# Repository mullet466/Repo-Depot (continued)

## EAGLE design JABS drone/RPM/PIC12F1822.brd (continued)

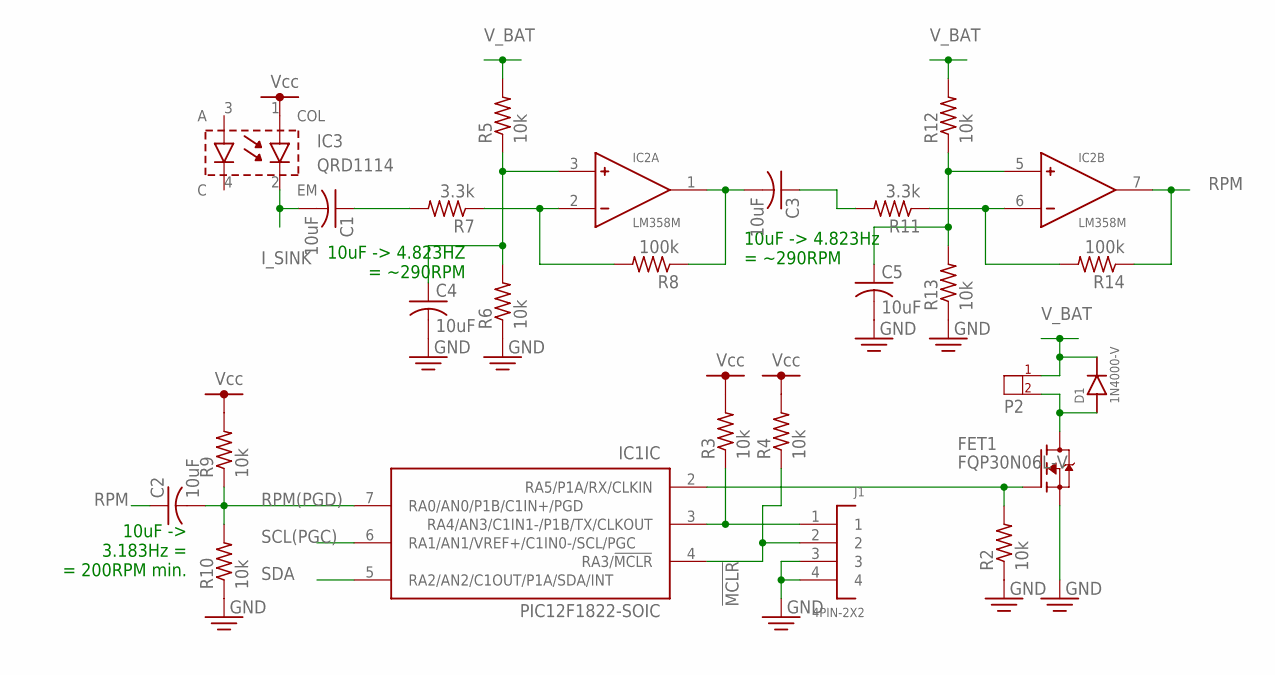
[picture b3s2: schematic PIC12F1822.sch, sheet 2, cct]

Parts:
C1, C2, C3, C4, C5: 10uF; C0805
D1: 1N4000-V; DIODE-V
FET1: FQP30N06L-V; TO220V
IC1: PIC12F1822-SOIC; 8-SOP
IC2: LM358M; 8-SOP
IC3: QRD1114
J1: 4PIN-2X2; 4P-2X2
P2: CONN-2P-PNI; B02B-PNISK
R2, R3, R4, R5, R6, R9, R10, R12, R13: 10k; R0805
R7, R11: 3.3k; R0805
R8, R14: 100k; R0805

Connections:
!MCLR: IC1.4 (RA3/!MCLR), J1.2, R4.1; also elsewhere on the board
GND: C4.2, C5.2, FET1.3 (S), J1.3, J1.4, R2.1, R6.1, R10.1, R13.1; also elsewhere on the board
I_SINK: C1.2, IC3.2 (EM); also elsewhere on the board
unnamed: FET1.1 (G), IC1.2 (RA5/P1A/RX/CLKIN), R2.2
unnamed: D1.A, FET1.2 (D), P2.2
unnamed: IC1.3 (RA4/AN3/C1IN1-/P1B/TX/CLKOUT), J1.1, R3.1
unnamed: C4.1, IC2.3 (+), R5.1, R6.2
unnamed: IC2.2 (-), R7.1, R8.2
unnamed: C1.1, R7.2
unnamed: C3.2, IC2.1 (OUT), R8.1
unnamed: C3.1, R11.2
unnamed: C5.1, IC2.5 (+), R12.1, R13.2
unnamed: IC2.6 (-), R11.1, R14.2
RPM: C2.1, IC2.7 (OUT), R14.1
RPM(PGD): C2.2, IC1.7 (RA0/AN0/P1B/C1IN+/PGD), R9.1, R10.2; also elsewhere on the board
SCL(PGC): IC1.6 (RA1/AN1/VREF+/C1IN0-/SCL/PGC); also elsewhere on the board
SDA: IC1.5 (RA2/AN2/C1OUT/P1A/SDA/INT); also elsewhere on the board
VCC: IC3.1 (COL), R3.2, R4.2, R9.2; also elsewhere on the board
V_BAT: D1.C, P2.1, R5.2, R12.2; also elsewhere on the board

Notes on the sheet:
10uF -> 4.823HZ = ~290RPM
10uF -> 4.823Hz = ~290RPM
10uF -> 3.183Hz = = 200RPM min.

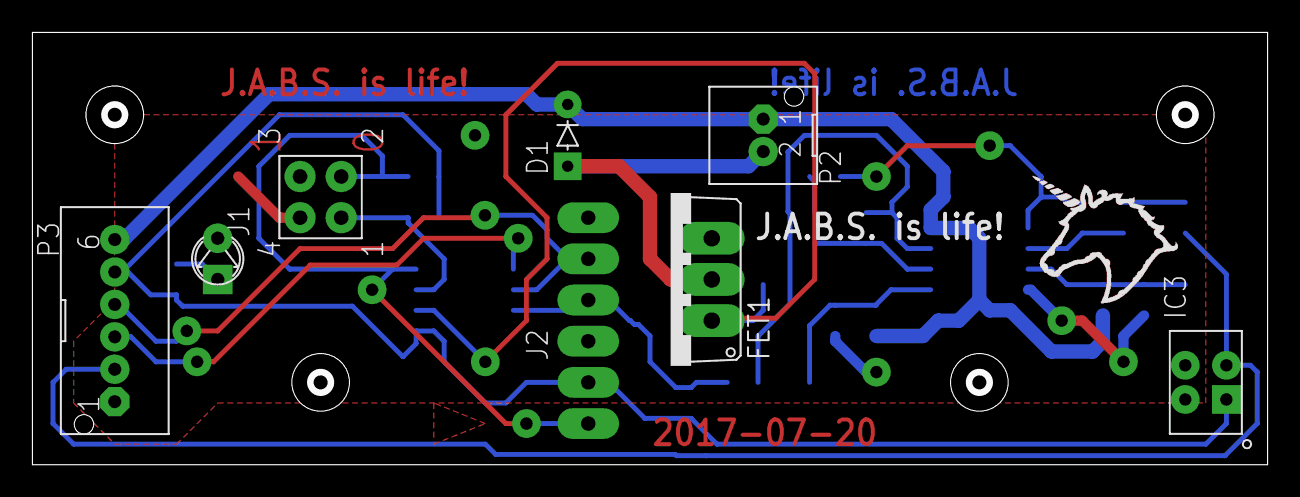
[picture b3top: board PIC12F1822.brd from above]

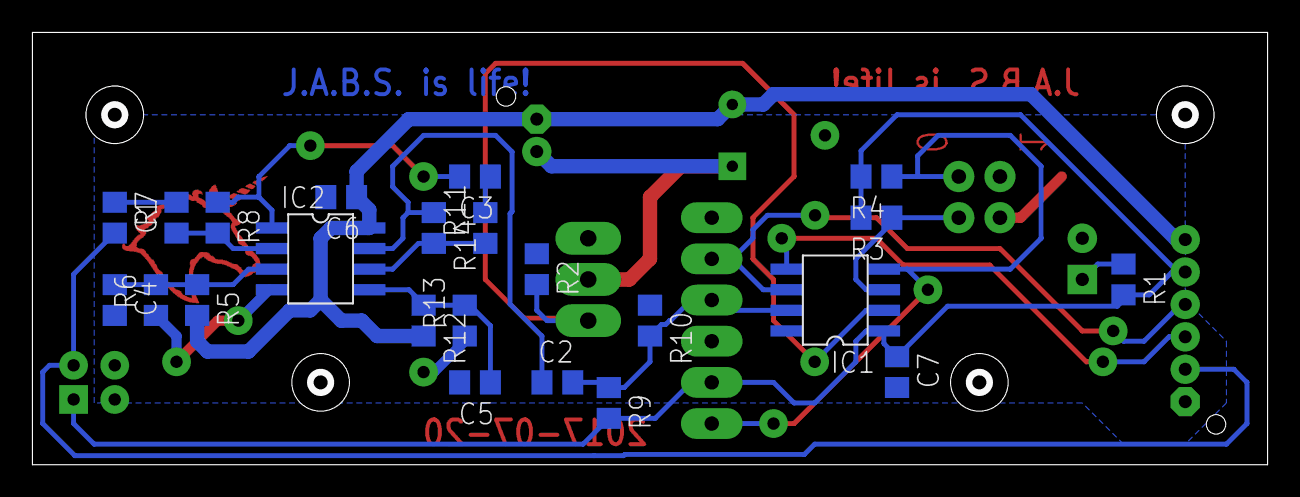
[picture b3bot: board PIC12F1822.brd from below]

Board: 2 copper layers, 75.8 x 26.3 mm, 37 parts (23 on the bottom side), 20 nets.

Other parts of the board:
U$16, U$17, U$18, U$19: #6-32
U$20: UNICORN-TOP
U$21: UNICORN-SCREEN

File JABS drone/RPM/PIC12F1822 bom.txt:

"Qty";"Value";"Device";"Package";"Parts";"Description";"";
"2";"100k";"R-US_R0805";"R0805";"R8, R14";"RESISTOR, American symbol";"";
"9";"10k";"R-US_R0805";"R0805";"R2, R3, R4, R5, R6, R9, R10, R12, R13";"RESISTOR, American symbol";"";
"3";"10uF";"C-USC0805";"C0805";"C1, C2, C3";"CAPACITOR, American symbol";"";
"1";"1N4000-V";"1N4000-V";"DIODE-V";"D1";"";"";
"2";"3.3k";"R-US_R0805";"R0805";"R7, R11";"RESISTOR, American symbol";"";
"1";"330";"R-US_R0805";"R0805";"R1";"RESISTOR, American symbol";"";
"1";"4PIN-2X2";"4PIN-2X2";"4P-2X2";"J1";"";"";
"1";"Bruno";"LED3MM";"LED3MM";"LED1";"";"";
"1";"CONN-2P-PNI";"CONN-2P-PNI";"B02B-PNISK";"P2";"";"";
"1";"CONN-6P-PNI";"CONN-6P-PNI";"B06B-PNISK";"P3";"";"";
"1";"FQP30N06L-V";"FQP30N06L-V";"TO220V";"FET1";"";"";
"1";"LM358M";"LM358M";"8-SOP";"IC2";"";"";
"1";"PIC12F1822-SOIC";"PIC12F1822-SOIC";"8-SOP";"IC1";"";"";
"1";"PICKIT3";"PICKIT3";"PICKIT3";"J2";"";"";
"1";"QRD1114";"QRD1114";"QRD1114";"IC3";"";"";

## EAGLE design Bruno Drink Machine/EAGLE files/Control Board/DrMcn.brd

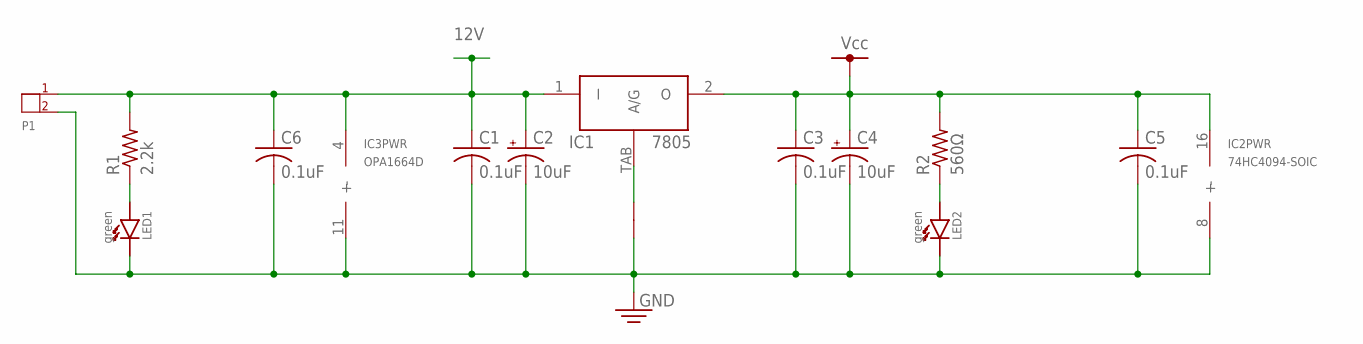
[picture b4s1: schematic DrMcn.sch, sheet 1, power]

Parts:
-1: SEPERATOR
C1, C3, C5, C6: 0.1uF; C0805
C2, C4: 10uF; E5-10,5
IC1: 7805; TO-252
IC2: 74HC4094-SOIC; 16-SOIC
IC3: OPA1664D; 14-SOP
LED1, LED2: green; 0603-LED
P1: CONN-2P-VL; B02P-VL
R1: 2.2k; R0805
R2: 560Ω; R0603

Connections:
12V: C1.1, C2.+, C6.1, IC1.1 (I), IC3.4 (+), P1.1, R1.2; also elsewhere on the board
GND: -1.P$1, C1.2, C2.-, C3.2, C4.-, C5.2, C6.2, IC2.8 (-), IC3.11 (-), LED1.C, LED2.C, P1.2; also elsewhere on the board
unnamed: LED2.A, R2.1
unnamed: LED1.A, R1.1
TAB: -1.P$2, IC1.TAB (A/G)
VCC: C3.1, C4.+, C5.1, IC1.2 (O), IC2.16 (+), R2.2; also elsewhere on the board

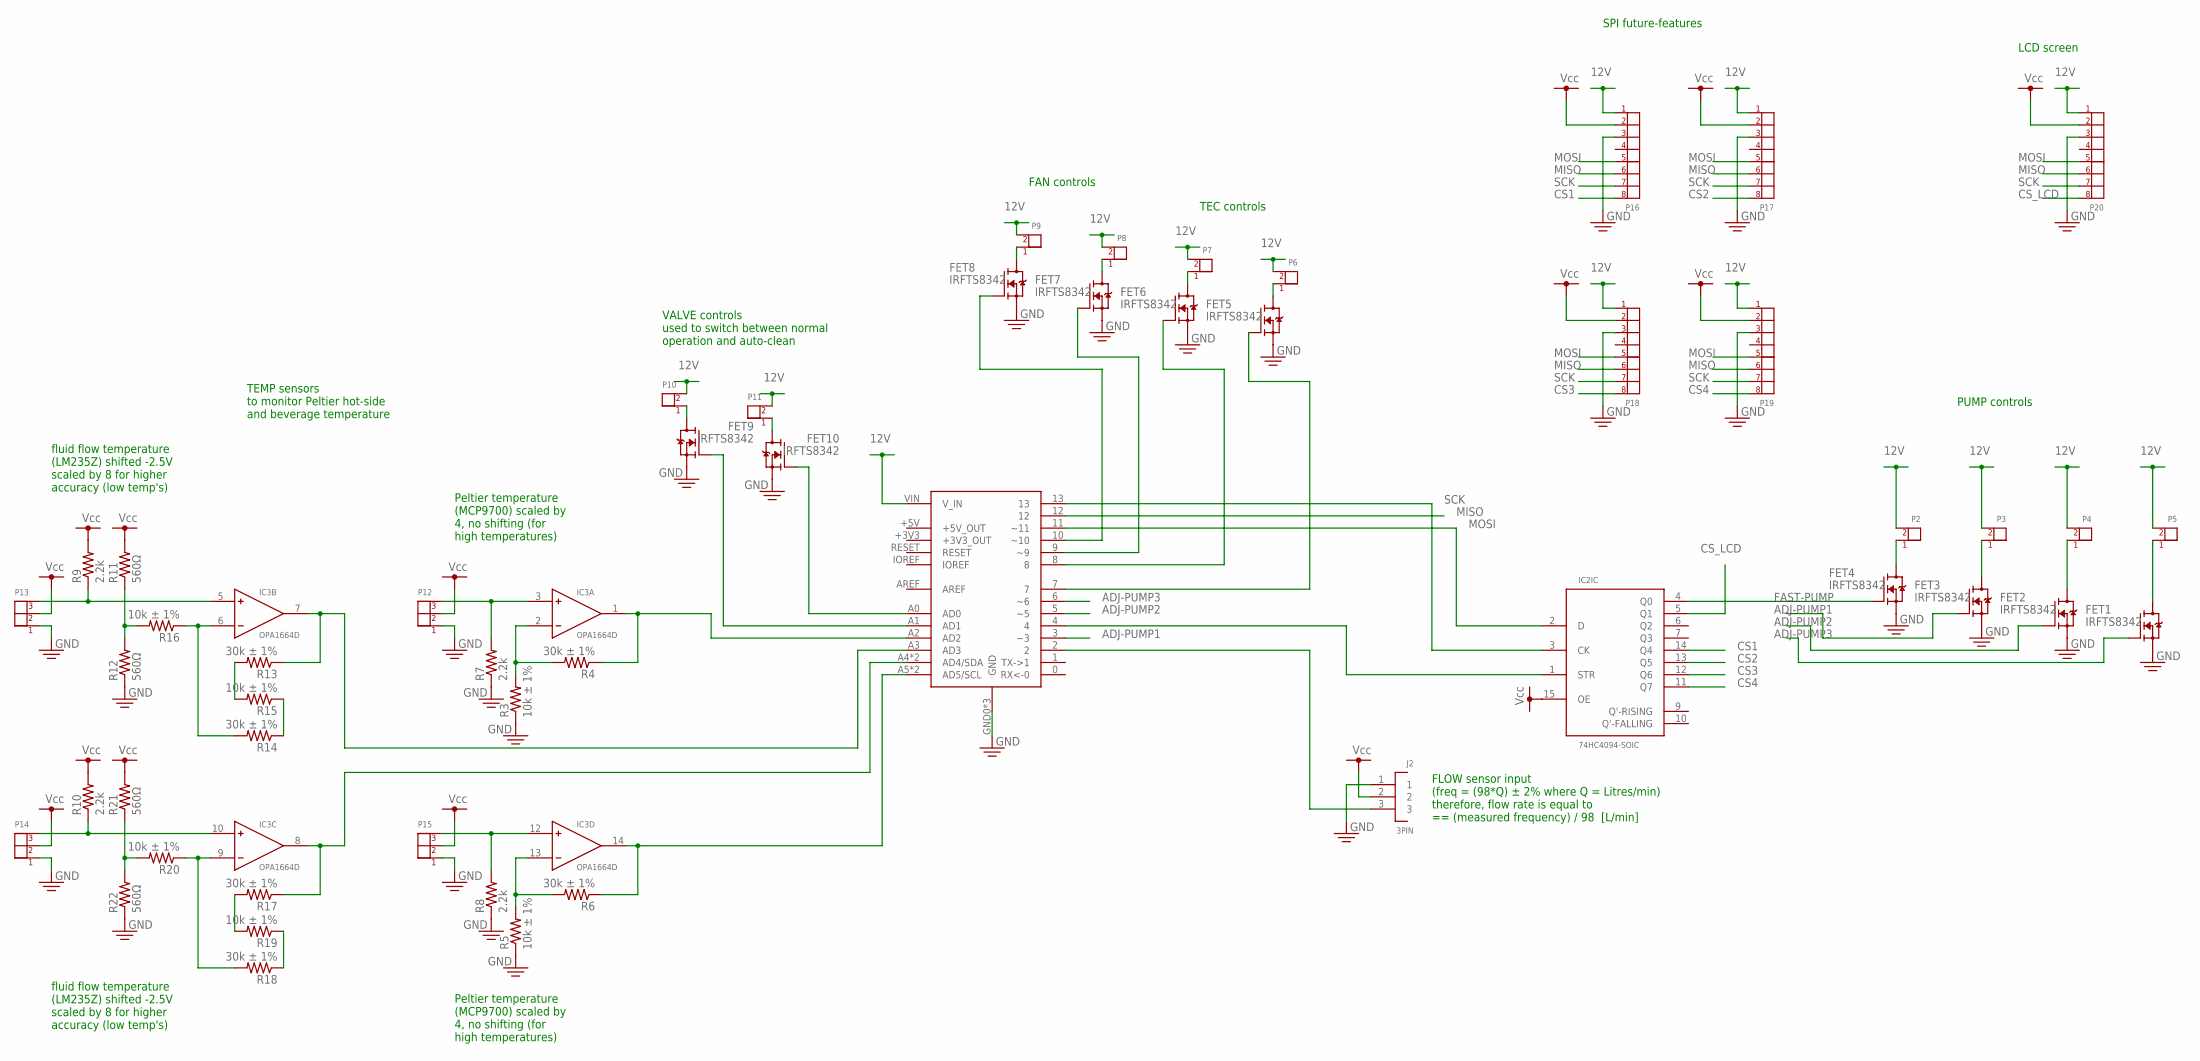
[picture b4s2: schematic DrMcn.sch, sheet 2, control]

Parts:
FET1, FET2, FET3, FET4, FET5, FET6, FET7, FET8, FET9, FET10: IRFTS8342; SOT23-6
IC2: 74HC4094-SOIC; 16-SOIC
IC3: OPA1664D; 14-SOP
J1: ARDUINO_UNO
J2: 3PIN; 3P
P2, P3, P4, P5, P8, P9, P10, P11: CONN-2P-PNI; B02B-PNISK
P6, P7: CONN-2P-VL; B02P-VL
P12, P13, P14, P15: CONN-3P-PNI; B03B-PNISK
P16, P17, P18, P19, P20: CONN-8P-PND; B08B-PND
R3, R5, R15, R16, R19, R20: 10k ± 1%; R0603
R4, R6, R13, R14, R17, R18: 30k ± 1%; R0603
R7, R8, R9, R10: 2.2k; R0603
R11, R12, R21, R22: 560Ω; R0603

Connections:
12V: J1.VIN (V_IN), P2.2, P3.2, P4.2, P5.2, P6.2, P7.2, P8.2, P9.2, P10.2, P11.2, P16.1, P17.1, P18.1, P19.1, P20.1; also elsewhere on the board
ADJ-PUMP1: FET3.3 (G), J1.3 (~3)
ADJ-PUMP2: FET2.3 (G), J1.5 (~5)
ADJ-PUMP3: FET1.3 (G), J1.6 (~6)
CS1: IC2.14 (Q4), P16.8
CS2: IC2.13 (Q5), P17.8
CS3: IC2.12 (Q6), P18.8
CS4: IC2.11 (Q7), P19.8
CS_LCD: IC2.5 (Q1), P20.8
FAST-PUMP: FET4.3 (G), IC2.4 (Q0)
GND: FET1.4 (S), FET2.4 (S), FET3.4 (S), FET4.4 (S), FET5.4 (S), FET6.4 (S), FET7.4 (S), FET8.4 (S), FET9.4 (S), FET10.4 (S), J1.GND0 (GND), J1.GND1 (GND), J1.GND2 (GND), J2.1, P12.1, P13.1, P14.1, P15.1, P16.3, P17.3, P18.3, P19.3, P20.3, R3.1, R5.1, R7.1, R8.1, R12.1, R22.1; also elsewhere on the board
MISO: J1.12, P16.6, P17.6, P18.6, P19.6, P20.6
MOSI: IC2.2 (D), J1.11 (~11), P16.5, P17.5, P18.5, P19.5, P20.5
unnamed: IC3.7 (OUT), J1.A3 (AD3), R13.1
unnamed: IC3.10 (+), P14.3, R10.1
unnamed: IC3.2 (-), R3.2, R4.2
unnamed: IC3.1 (OUT), J1.A2 (AD2), R4.1
unnamed: FET4.1 (D), FET4.2 (D), FET4.5 (D), FET4.6 (D), P2.1
unnamed: FET3.1 (D), FET3.2 (D), FET3.5 (D), FET3.6 (D), P3.1
unnamed: FET2.1 (D), FET2.2 (D), FET2.5 (D), FET2.6 (D), P4.1
unnamed: FET1.1 (D), FET1.2 (D), FET1.5 (D), FET1.6 (D), P5.1
unnamed: FET7.3 (G), J1.9 (~9)
unnamed: J1.2, J2.3
unnamed: FET9.1 (D), FET9.2 (D), FET9.5 (D), FET9.6 (D), P10.1
unnamed: FET5.1 (D), FET5.2 (D), FET5.5 (D), FET5.6 (D), P6.1
unnamed: FET10.1 (D), FET10.2 (D), FET10.5 (D), FET10.6 (D), P11.1
unnamed: FET6.1 (D), FET6.2 (D), FET6.5 (D), FET6.6 (D), P7.1
unnamed: FET7.1 (D), FET7.2 (D), FET7.5 (D), FET7.6 (D), P8.1
unnamed: FET8.3 (G), J1.10 (~10)
unnamed: FET8.1 (D), FET8.2 (D), FET8.5 (D), FET8.6 (D), P9.1
unnamed: FET6.3 (G), J1.8
unnamed: FET5.3 (G), J1.7
unnamed: FET9.3 (G), J1.A1 (AD1)
unnamed: FET10.3 (G), J1.A0 (AD0)
unnamed: IC3.13 (-), R5.2, R6.2
unnamed: IC3.5 (+), P13.3, R9.1
unnamed: IC3.8 (OUT), J1.A4 (AD4/SDA), J1.SDA (AD4/SDA), R17.1
unnamed: IC3.14 (OUT), J1.A5 (AD5/SCL), J1.SCL (AD5/SCL), R6.1
unnamed: IC3.3 (+), P12.3, R7.2
unnamed: R11.1, R12.2, R16.2
unnamed: IC2.1 (STR), J1.4
unnamed: IC3.12 (+), P15.3, R8.2
unnamed: IC3.6 (-), R14.2, R16.1
unnamed: IC3.9 (-), R18.2, R20.1
unnamed: R20.2, R21.1, R22.2
unnamed: R13.2, R15.2
unnamed: R14.1, R15.1
unnamed: R17.2, R19.2
unnamed: R18.1, R19.1
SCK: IC2.3 (CK), J1.13, P16.7, P17.7, P18.7, P19.7, P20.7
VCC: IC2.15 (OE), J2.2, P12.2, P13.2, P14.2, P15.2, P16.2, P17.2, P18.2, P19.2, P20.2, R9.2, R10.2, R11.2, R21.2; also elsewhere on the board

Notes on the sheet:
PUMP controls
FLOW sensor input (freq = (98*Q) ± 2% where Q = Litres/min) therefore, flow rate is equal to == (measured frequency) / 98 [L/min]
TEC controls
FAN controls
VALVE controls used to switch between normal operation and auto-clean
TEMP sensors to monitor Peltier hot-side and beverage temperature
SPI future-features
Peltier temperature (MCP9700) scaled by 4, no shifting (for high temperatures)
fluid flow temperature (LM235Z) shifted -2.5V scaled by 8 for higher accuracy (low temp's)
LCD screen

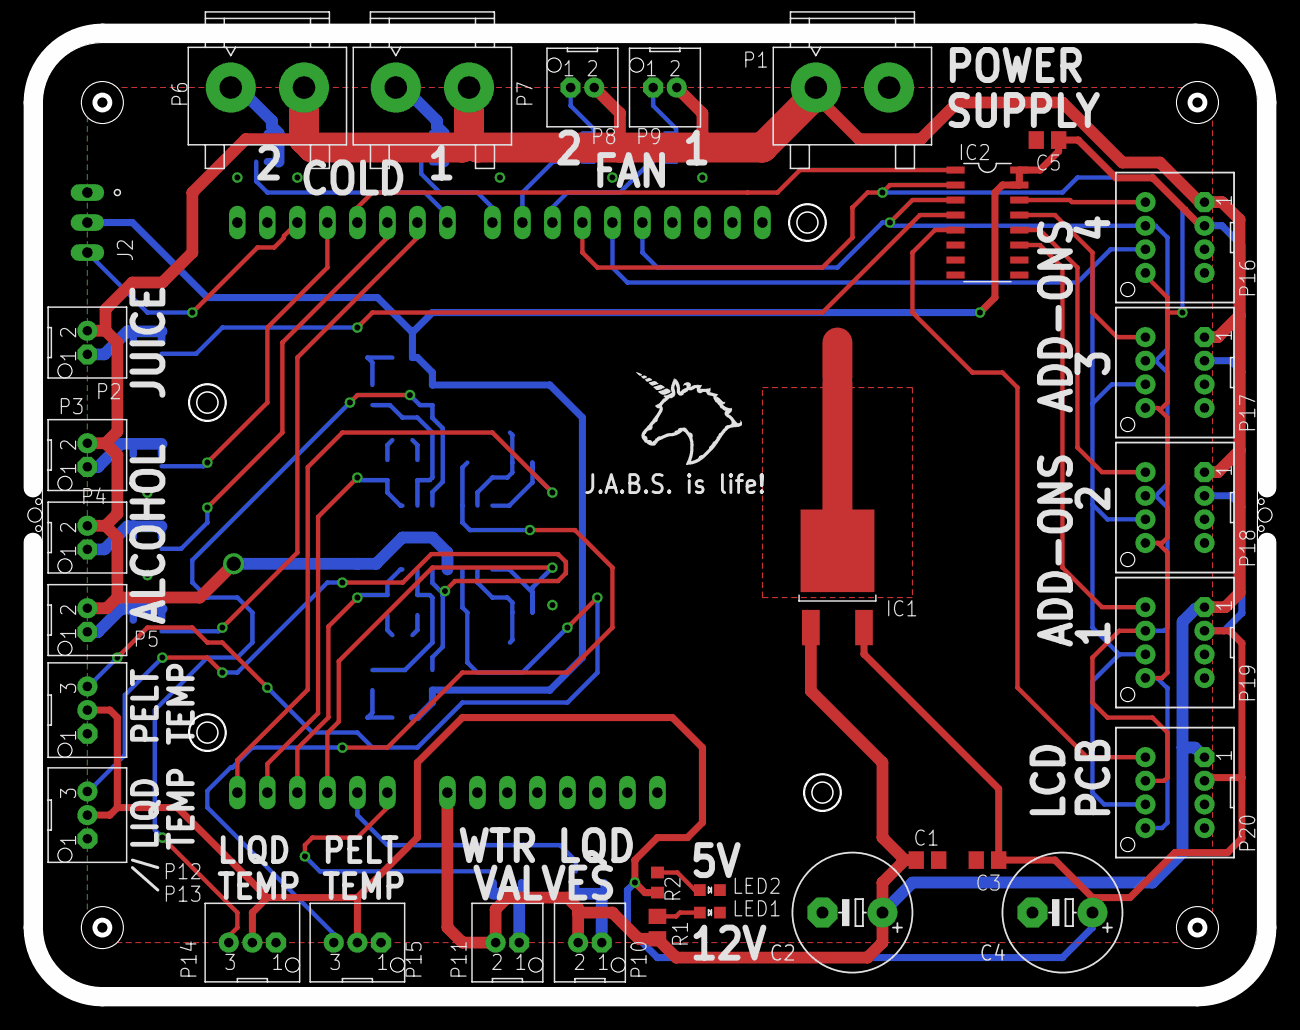
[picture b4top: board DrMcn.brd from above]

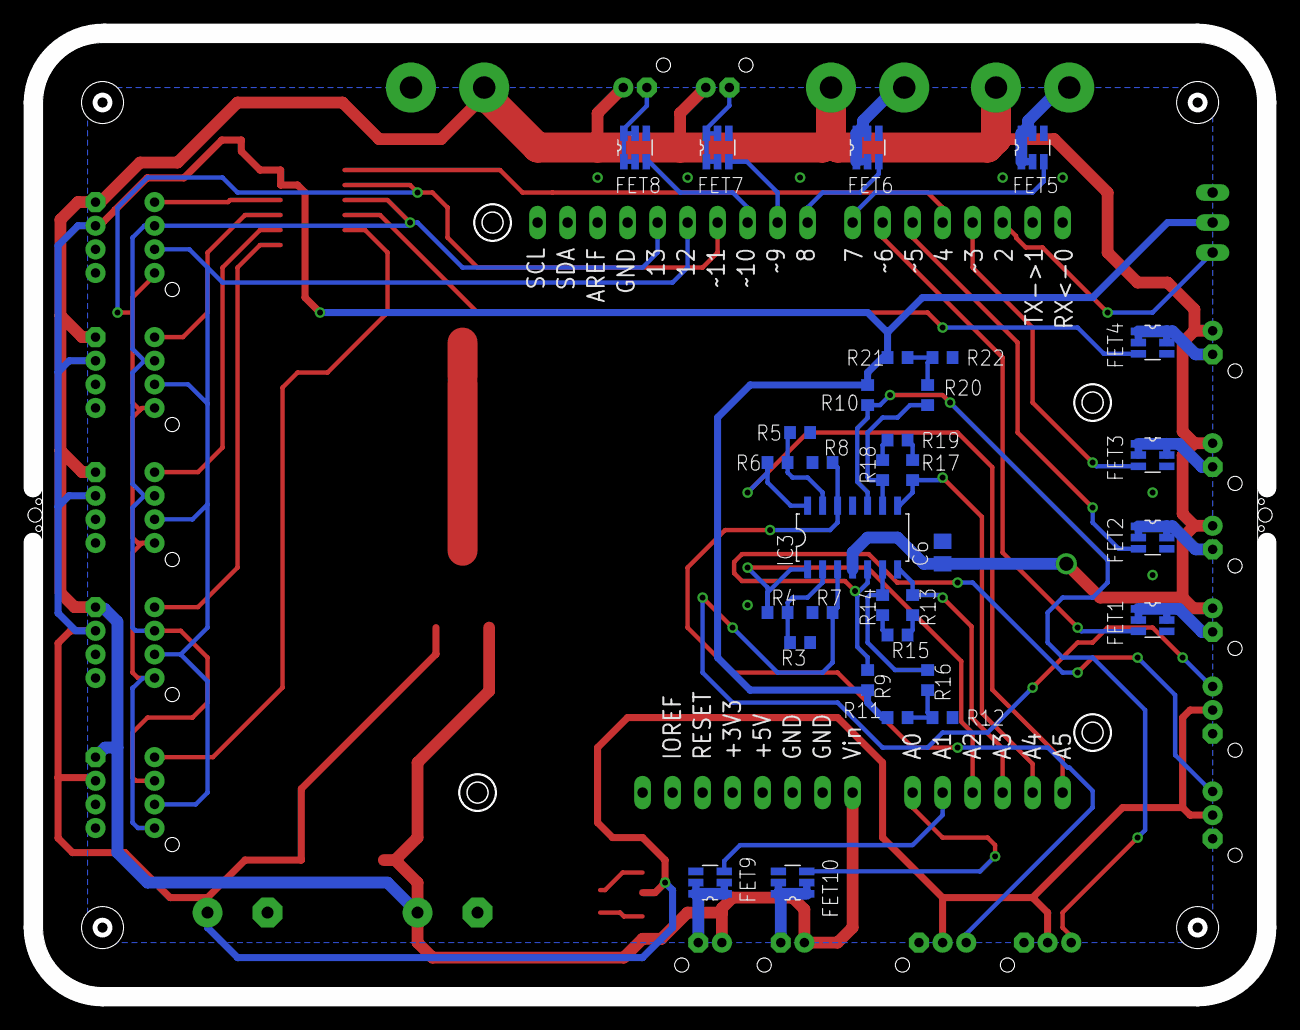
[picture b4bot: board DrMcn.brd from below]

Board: 2 copper layers, 104.5 x 81.6 mm, 72 parts (33 on the bottom side), 54 nets.

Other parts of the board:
U$43, U$44, U$45, U$46: #6-32
U$49: UNICORN-SCREEN
U$50: JABS

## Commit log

2018-12-12 testing this thing with a testy test string
2018-12-12 Didn't need that test file, removing it now. Will put actual files into repo tomorrow.
2018-12-12 Adding info for EAGLE Project for 2019, "Bruno's Drink Machine"
2018-12-12 removing README.md, or trying to...
2018-12-14 Added BOM with some parts. Will organize it better when more parts are entered.
2019-02-02 Added Bruno's Drink Machine Shield schematic & board (finally)
2019-02-02 Removed old (bad) folder. Added correct BOM and info files.
2019-02-02 "Fixed" the directory tree to be a bit more organized.
2019-02-02 Deleting duplicate files left from last bad commit. Now it's organized :)
2019-03-09 addind 16bit LCD display PCB, converting to 4layer board soon
2019-03-16 airwires routed on LCD board; need to fix DRC errors before ordering PCBs
2019-03-23 fixed all DRC issues, Gerber files ready for ordering
2019-03-23 added JABS Drone (in it's current state) to repo -- needs software/testing also added condense.t (to condense V-One milling code) in LCD folder
2019-03-27 fixed some minor silkscreen issues, moved USB connector to the edge of the PCB
2019-03-27 added document for SPI commands to LCD board, and an image showing overall look
2019-04-11 added pics of v1.0 PCB -- straight from the mail
2019-04-14 added change log and removed V-One milling gCode files
2019-04-15 updated change-request log with LCB sub-PCB (for physical LCD positioning)
2019-04-20 added 1 change, wanna make sure it's not lost
2019-04-20 made some of the changes; not all (will need to go through change list and confirm later)
2019-04-27 added another change (40p connector wrong) in change log; wrote some code
2019-06-11 commit before merge
2019-06-11 had to duplicate a connector on the board to merge; deleted duplicate now (back to normal)
